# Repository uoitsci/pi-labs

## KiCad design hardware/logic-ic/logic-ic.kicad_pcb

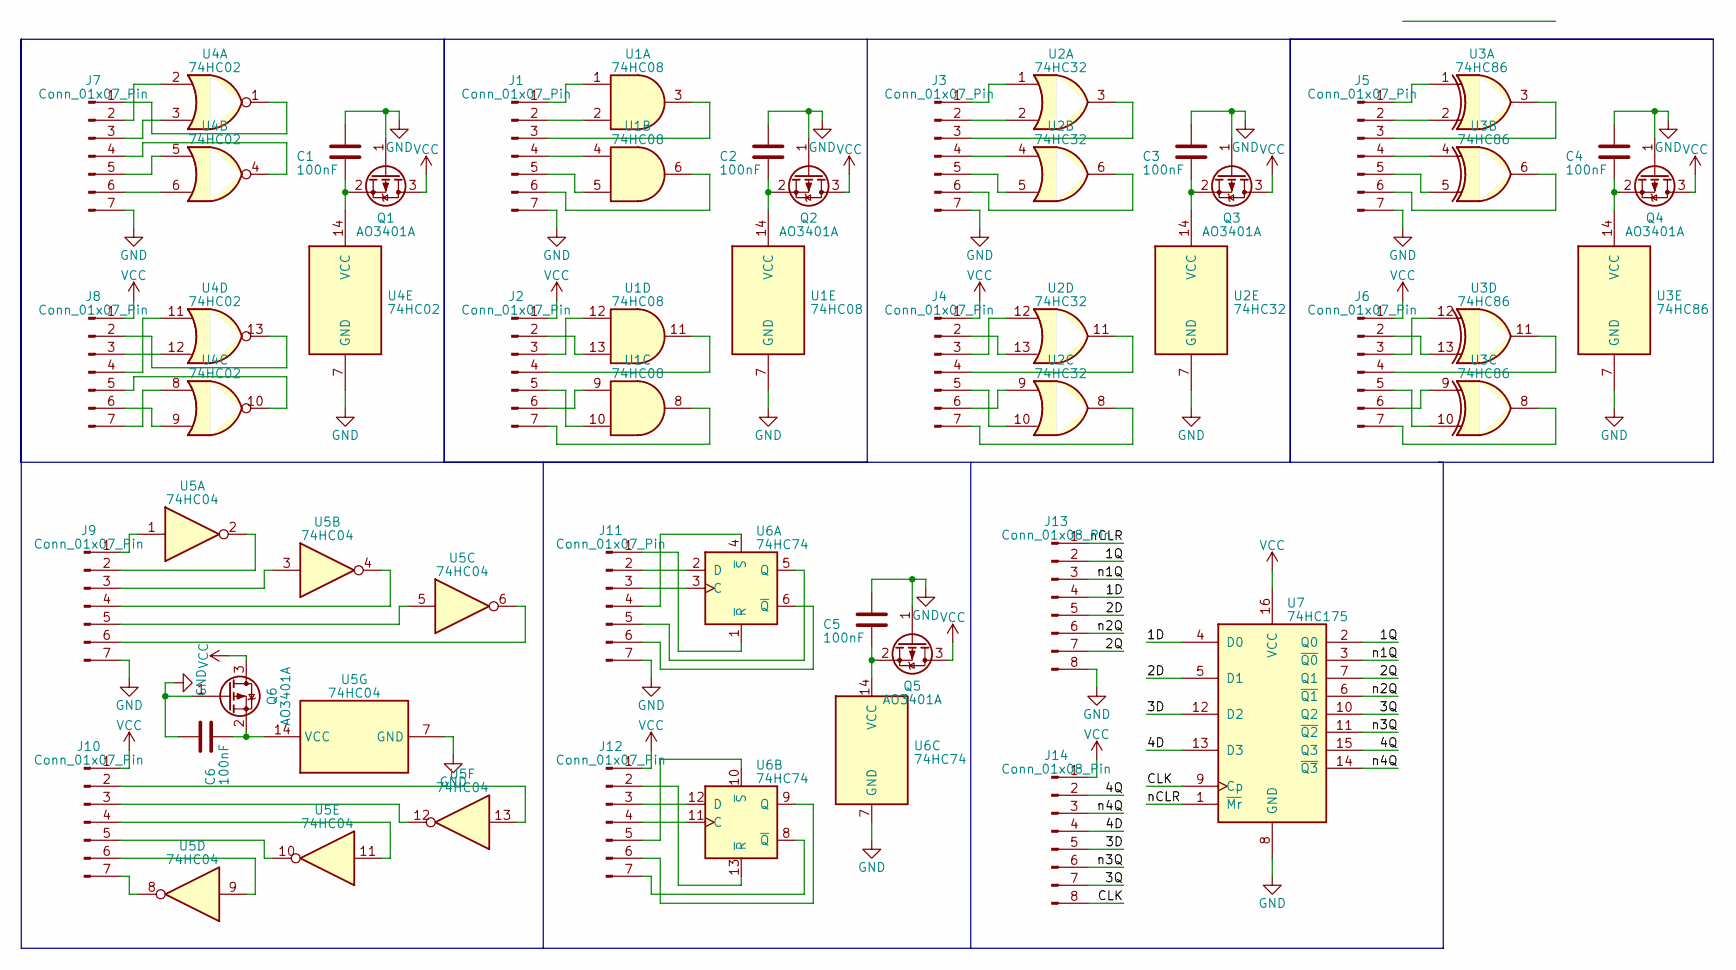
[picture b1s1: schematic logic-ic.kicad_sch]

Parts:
C1, C2, C3, C4, C5, C6: 100nF; C_0402_1005Metric
J1, J2, J3, J4, J5, J6, J7, J8, J9, J10, J11, J12: Conn_01x07_Pin; PinHeader_1x07_P2.54mm_Vertical_1
J13, J14: Conn_01x08_Pin; PinHeader_1x08_P2.54mm_Vertical
Q1, Q2, Q3, Q4, Q5, Q6: AO3401A; SOT-23; LCSC C15127
U1: 74HC08; SOIC-14_3.9x8.7mm_P1.27mm
U2: 74HC32; SOIC-14_3.9x8.7mm_P1.27mm
U3: 74HC86; SOIC-14_3.9x8.7mm_P1.27mm
U4: 74HC02; SOIC-14_3.9x8.7mm_P1.27mm
U5: 74HC04; SOIC-14_3.9x8.7mm_P1.27mm
U6: 74HC74; SOIC-14_3.9x8.7mm_P1.27mm
U7: 74HC175; SOIC-16_3.9x9.9mm_P1.27mm

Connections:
/1D: J13.4, U7.4 (D0)
/1Q: J13.2, U7.2 (Q0)
/2D: J13.5, U7.5 (D1)
/2Q: J13.7, U7.7 (Q1)
/3D: J14.5, U7.12 (D2)
/3Q: J14.7, U7.10 (Q2)
/4D: J14.4, U7.13 (D3)
/4Q: J14.2, U7.15 (Q3)
/CLK: J14.8, U7.9 (Cp)
/n1Q: J13.3, U7.3 (~Q0)
/n2Q: J13.6, U7.6 (~Q1)
/n3Q: J14.6, U7.11 (~Q2)
/n4Q: J14.3, U7.14 (~Q3)
/nCLR: J13.1, U7.1 (~Mr)
GND: C1.1, C2.1, C3.1, C4.1, C5.1, C6.1, J1.7, J3.7, J5.7, J7.7, J9.7, J11.7, J13.8, Q1.1 (G), Q2.1 (G), Q3.1 (G), Q4.1 (G), Q5.1 (G), Q6.1 (G), U1.7 (GND), U2.7 (GND), U3.7 (GND), U4.7 (GND), U5.7 (GND), U6.7 (GND), U7.8 (GND)
unnamed: J1.1, U1.1
unnamed: J1.2, U1.2
unnamed: J1.3, U1.3
unnamed: J1.4, U1.4
unnamed: J1.5, U1.5
unnamed: J1.6, U1.6
unnamed: J2.2, U1.13
unnamed: J2.3, U1.12
unnamed: J2.4, U1.11
unnamed: J2.5, U1.10
unnamed: J2.6, U1.9
unnamed: J2.7, U1.8
unnamed: J3.1, U2.1
unnamed: J3.2, U2.2
unnamed: J3.3, U2.3
unnamed: J3.4, U2.4
unnamed: J3.5, U2.5
unnamed: J3.6, U2.6
unnamed: J4.2, U2.13
unnamed: J4.3, U2.12
unnamed: J4.4, U2.11
unnamed: J4.5, U2.10
unnamed: J4.6, U2.9
unnamed: J4.7, U2.8
unnamed: J5.1, U3.1
unnamed: J5.2, U3.2
unnamed: J5.3, U3.3
unnamed: J5.4, U3.4
unnamed: J5.5, U3.5
unnamed: J5.6, U3.6
unnamed: J6.2, U3.13
unnamed: J6.3, U3.12
unnamed: J6.4, U3.11
unnamed: J6.5, U3.10
unnamed: J6.6, U3.9
unnamed: J6.7, U3.8
unnamed: J7.1, U4.1
unnamed: J7.2, U4.2
unnamed: J7.3, U4.3
unnamed: J7.4, U4.4
unnamed: J7.5, U4.5
unnamed: J7.6, U4.6
unnamed: J8.2, U4.13
unnamed: J8.3, U4.12
unnamed: J8.4, U4.11
unnamed: J8.5, U4.10
unnamed: J8.6, U4.9
unnamed: J8.7, U4.8
unnamed: J9.1, U5.1
unnamed: J9.2, U5.2
unnamed: J9.3, U5.3
unnamed: J9.4, U5.4
unnamed: J9.5, U5.5
unnamed: J9.6, U5.6
unnamed: J10.2, U5.13
unnamed: J10.3, U5.12
unnamed: J10.4, U5.11
unnamed: J10.5, U5.10
unnamed: J10.6, U5.9
unnamed: J10.7, U5.8
unnamed: J11.1, U6.1 (~R)
unnamed: J11.2, U6.2 (D)
unnamed: J11.3, U6.3 (C)
unnamed: J11.4, U6.4 (~S)
unnamed: J11.5, U6.5 (Q)
unnamed: J11.6, U6.6 (~Q)
unnamed: J12.2, U6.13 (~R)
unnamed: J12.3, U6.12 (D)
unnamed: J12.4, U6.11 (C)
unnamed: J12.5, U6.10 (~S)
unnamed: J12.6, U6.9 (Q)
unnamed: J12.7, U6.8 (~Q)
unnamed: C1.2, Q1.2 (S), U4.14 (VCC)
unnamed: C2.2, Q2.2 (S), U1.14 (VCC)
unnamed: C3.2, Q3.2 (S), U2.14 (VCC)
unnamed: C4.2, Q4.2 (S), U3.14 (VCC)
unnamed: C5.2, Q5.2 (S), U6.14 (VCC)
unnamed: C6.2, Q6.2 (S), U5.14 (VCC)
VCC: J2.1, J4.1, J6.1, J8.1, J10.1, J12.1, J14.1, Q1.3 (D), Q2.3 (D), Q3.3 (D), Q4.3 (D), Q5.3 (D), Q6.3 (D), U7.16 (VCC)

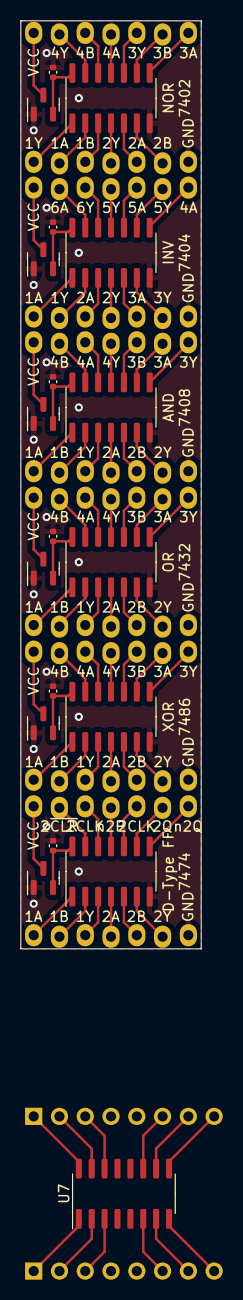
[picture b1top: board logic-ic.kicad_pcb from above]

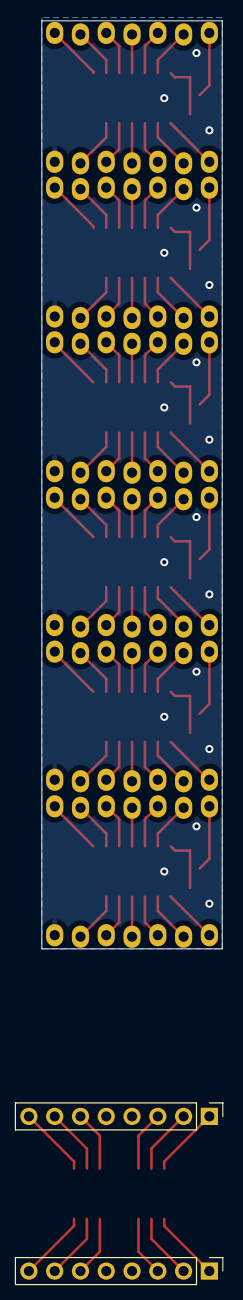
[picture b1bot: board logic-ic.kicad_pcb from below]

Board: 2 copper layers, 17.8 x 91.4 mm, 33 parts (14 on the bottom side), 94 nets.

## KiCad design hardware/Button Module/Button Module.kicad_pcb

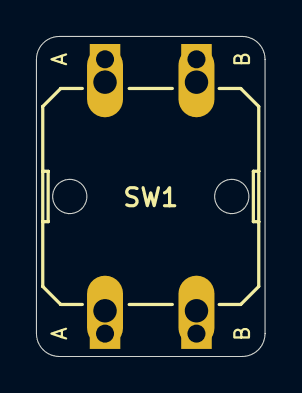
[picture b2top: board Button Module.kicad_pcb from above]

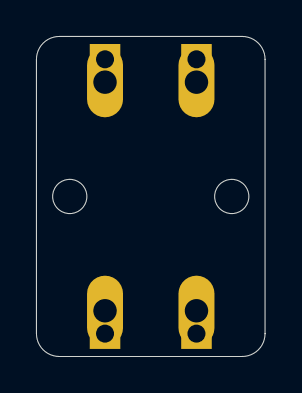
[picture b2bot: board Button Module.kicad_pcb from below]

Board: 2 copper layers, 12.7 x 17.8 mm, 5 parts (4 on the bottom side), 2 nets, no tracks yet.

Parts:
J1, J2: A; PinHeader_1x01_P2.54mm_Vertical
J5, J6: B; PinHeader_1x01_P2.54mm_Vertical
SW1: B3F-4055; B3F-40XX

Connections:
unnamed: J1.1, J2.1, SW1.1
unnamed: J5.1, J6.1, SW1.2

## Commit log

2014-12-07 Adding the .gitignore
2014-12-08 Fixed submodule, updated layouts to work with Hugo >= 0.11.0
2014-12-08 Modified shortcode usage to stop code blocks from being wrapped in paragraph tags. Hugo issue #565.
2014-12-08 Fixed a number of mis-spellings and some grammatical errors.
2014-12-08 Point Hugo to the new site URL.
2014-12-08 Added MathJax support.
2014-12-11 Updated image shortcode to handle HiDPI images and tweaked some of the output it generates.
2014-12-11 Rewrite of GPIO lab. Changed illustrations to Model B+ and updated the circuits. All images should look good in HiDPI.
2014-12-11 Forgot the images...
2014-12-18 Added assets directory to store pre-processed content.
2015-01-16 Clarified some pin designations to avoid student confusion and fixed one typo
2015-01-16 Updated Fritzing images to reflect correct header/breadboard orientation, and wiring pattern with common power/ground
2015-01-16 Added content to the About Python lab
2015-01-28 Added half adder content to circuit lab (which is new), more to come for this lab
2015-01-28 Added circuit lab document itself
2015-01-28 Some changes to circuit lab that were not saved (2)
2015-01-28 Some changes to circuit lab that were not saved (3)
2015-01-28 Some changes to circuit lab that were not saved (4)
2015-01-28 Some changes to circuit lab that were not saved (5)
2015-01-28 Some changes to circuit lab that were not saved (6)
2015-01-28 Some changes to circuit lab that were not saved (7)
2015-01-28 Added full adder content to circuit lab
2015-02-02 Added circuit and wiring diagrams to assets folder
2015-02-09 Heavily modified circuit lab, site layout, and images.
2016-01-19 Updated first lab with references to incorrect login/homedir details
2016-01-19 Fixed Hugo build errors, use GFM-style highlight tags, switch to Python 3-compatible syntax since it's not 2005 anymore.
2016-01-19 Added figure, more Py3 fixes, notes on username/password of users.
2016-02-17 Updated seven segment lab to i2C
2016-02-17 Added a second seven segment display lab
2016-02-17 Separated the HA/FA circuit labs into two labs
2016-02-17 Renamed some of the files, updated lab order
2016-02-17 Some missing image files
2016-02-17 fixed an error in seven segment lab code
2016-02-17 More bugs
2016-02-17 more typos
2016-02-17 Elaborated on PUD_DOWN and PUD_UP in GPIO
2016-02-17 Files did not update
2016-02-17 Added Fritzing files
2016-02-17 Touch ups in headers
2016-02-17 Added reminder about pull up resistors to 7seg lab#2
2016-02-17 Dummy change to test web hook
2016-02-17 Another change to test the web hook
2016-02-18 Added how to download support code for 7seg lab
2016-02-18 Clarified instructions - test code executed after cobbler stuff
2016-02-18 Fixed a typo regarding the test program
2016-02-18 Missing single quote
2016-03-28 Fixed a bug in the assembly language lab
2017-01-18 Update username and password instructions
2017-11-30 Updated to new MathJax CDN.
2017-11-30 Removed text references to 5V since the new chips are capable of operating at 3V3 and the Pi's GPIO won't tolerate 5V.
2017-11-30 Removed LD33CV regulators from Fritzing diagrams.
2017-11-30 Optimized PNG files.
2018-01-29 Updated lab 3, which had a bad circuit. Also, used more sensible GPIO pins to be easier to wire up
2018-01-29 Updated lab 3 to match new GPIO pins
2018-01-29 Updated the diagram for lab 03
2018-01-29 Made a mistake in one of the diagrams for lab 03
2018-03-07 Updated seven-segment display lab to use new software API
2018-03-07 Fixed some errors in the seven-segment lab #1 code
2018-03-07 Fixed another error
2018-06-04 Fixed I2C backpack circuit, added Dockerfile and makefile.
2018-06-04 Dockerfile moved the static files to the wrong location.
2018-06-04 Fixed generation issues.
2018-06-04 Fixed rendering.
2018-06-04 Moved theme setting to config.toml
2018-06-05 Accidentally the baseURL.
2018-06-05 Accidentally it again.
2018-06-05 Fixed up the layout.
2018-06-06 Now utilizing Hugo's page resources and image processing.
2018-06-06 Garbage collect old images on build.
2018-06-07 Slimmed down Docker image.
2018-06-07 Fixed incorrect resistor value.
2019-01-21 Update to reference new 3B+ features and quirks.
2019-01-21 Hugo now requires glibc++ to function.
2019-01-21 Point pages back towards production site.
2019-01-22 Fix diagram error. Button went to GND instead of 3V3.
2020-01-27 Update to latest Hugo
2020-01-28 Various fixes, added zooming for images.
2020-02-03 Added button module KiCAD files.
2020-02-03 Updated servo breadboard diagram to 3.3V.
2020-02-04 Added note regarding switch from 5V -> 3.3V power
2020-02-04 Fixed MathJax rendering, SSD tables.
2020-02-04 Update config, use CM definition list syntax, updated table.
2020-02-04 Clean up some formatting.
2020-02-04 Updated SSD labs to use 3.3V, update layout and config, customize fonts.
2020-02-05 Add note about mixing spaces and tabs.
2020-02-05 Fix logo rendering.
2020-02-05 Migrate back to shortcodes.
2020-02-05 Bump Hugo version.
2020-02-05 Removed videos, fix dockerignore file so custom SCSS is included.
2023-03-29 Updated instructions for RPi 4 boards
2023-03-29 Force integer division (closes #4)
2023-10-27 Fixing the diagram and updating the content
    - Fixes the flipped +/- colour label on the half/full adder breadboard
    - Fixes the +/- Red/Black cable on servo
    - Changing GPIO mode to BCM
    - Updating the sevensegment library to the new up-to-date library
    - Updating the ARM Assembler code to accomodate the 64-bit OS
2023-11-01 Add missing PNG files
2023-11-01 Updated the Retina images
2024-01-12 Update login format and revert ARM assembly to 32-bit
2024-01-18 Fixed Lab 1 Content
    - Reworded some paragraphs because students get lost on where the IDLE is
    - Replaced F5 to Run Module
    - Specified the "Shell"
    - Replaced New Window to New File
    - Changed code since comma separator does not print newline anymore.
2024-01-18 Fixed lab 1 error.
2024-02-20 Changed Assembly from 32-bit to 64-bit
2024-02-26 Fixed Indentation error and adding new information
2024-03-11 Updated and tweaked 7-SD Labs
    - Changed the 'python' in the bash command to 'python3'.
    - Specified that the bash command should run in the bash terminal and not the IDLE shell.
    - Made the 4 bullet points exercise into 2 points instead, with additional sub-bullet points.
    - Clear up the [0,9999] / [0,FFFF] in the exercise points
    - Included the hint into the "Message" highlight
2024-03-14 Updated and Specified SSD Part 1
    - Updated the description for the test program to match the result
    - Specified that the 1000 is in hexadecimal, not in decimal.
2024-03-18 Clarified 7-SD Part 2
    - Clarified the goal of the program and how it functions with the Hold, Stop, and Go.
2024-03-20 Updated 7-SD Part 2
    - Removed the old message hint regarding the GPIO.PUD_UP.
2024-03-26 Added Content to Assembly
    - Added explanation on Instructions and Branching
    - Renamed "Basic Arithmetic" to "Exercise #1"
    - Added one more exercise on to the assembly.
2024-04-30 Re-implementation of PiServer conversion script (+ customizations) using pi-gen
